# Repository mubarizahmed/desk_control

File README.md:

# desk-control

This is a simple physical widget that sits on your desk and allows you to perform some basic productivity tasks. It works independently of your computer or phone and hence, _in theory_, it should help you focus on your work. It is a work in progress and I will be adding more features as I go along.

<div align="center" style="display: flex; justify-content: center; align-items: center;">

</div>

## Features

- **Current Time** - Displays the current time in a 24-hour format.
- **Weather** - Displays the current temperature, wind, and weather condition (sunny, cloudy, etc.) for a given location.
- **Pomodoro Timer** - A simple timer that helps you focus on your work for a some template amount of time and then take a break. Current implementation is 25 minutes of work and 5 minutes of break. You can change this in the code.
- **Calendar** - Displays the current date and the next 2 events from your Google Calendar. You need to set up a Google script to get the events from your calendar. See the [Google Calendar Setup](#google-calendar-setup) section below.

- **Spotify Control** - Control your Spotify playback (play, pause, next, previous) from the widget.

- **Todoist Integration** - View and complete your upcoming tasks from Todoist.

- **PCB Design** - Single PCB design that can be printed on PCBWay or JLCPCB.

## Planned Features

- **Housing** - 3D printed housing for the PCB and screen.

- **Sensor Integration** - Add more sensors to the project - maybe a temperature sensor, humidity sensor, etc. to get more data from the environment.

- **Widget Details** - Widgets will be clickable and will show more details about the current state. For example, the weather widget will show the hourly forecast for the next 24 hours, the calendar widget will show the events for the next week, etc.

## Hardware Setup (Work in Progress)

The hardware setup is a work in progress. I will be updating this section as I go along. Currently, the hardware setup is:

- **Microcontroller** - ESP32-DevKitC-v4
- **Display** - 2.4" TFT LCD (ILI9341) with SPI interface
- **Rotary Encoder** - KY-040 rotary encoder with push button.

A custom PCB has been designed but not yet tested. The schematic and KiCAD project files are available in the `eda` folder.

<div align="center">
  
</div>

[Schematic](eda/desk_control_schematic_color.png)

<div align="center" style="display: flex; justify-content: center; align-items: center;">

</div>

[PCB Front](eda/front.png) | [PCB Back](eda/back.png)

[KiCAD Project](eda/desk_control)

Pin definitions are given in [here](/main/pin_definitions.h).

## Software Setup

ESP IDF is used to program the ESP32. The project can be configured using `idf.py menuconfig`. The following configuration options are most relevant:

- **ESP_WIFI_SSID** - The SSID of the Wi-Fi network to connect to.
- **ESP_WIFI_PASSWORD** - The password of the Wi-Fi network to connect to.
- **CALENDAR_URL** - The URL of the Google script that returns the events from your calendar.

## Mock UI

The mock UI is a simple representation of what the final UI will look like. It is not a final design and will be updated as I go along. The current design is a simple grid layout with a monotype font which makes absolute positioning of the elements easy.

<div align="center">
  
</div>

## Progress

The project is being prototyped on a breadboard and the hardware setup is a work in progress. The software is being developed in parallel. The current status of the project is shown below:

<div align="center">
  
</div>

## Google Calendar Setup

To get the events from your Google Calendar, you need to set up a Google script that will fetch the events and return them in a JSON format. The script should be deployed as a web app and the URL should be added to the code. The following steps will help you set up the Google script:

1. Go to [Google Apps Script](https://script.google.com/) and create a new project.
2. Copy and paste the code from this (file)[https://github.com/mubarizahmed/desk_control/blob/main/other/calendar.gs] into the script editor
3. Save the project and give it a name.
4. Click on the `Deploy` button and select `New deployment`.
5. Select `Web app` and give it a name.
6. Select `Anyone` under `Who has access` and click on `Deploy`.
7. Authorize the script to access your Google Calendar.
8. Copy the URL of the web app and paste it in the code where it says `CALENDAR_URL`.
9. Save the code and run the script to test it. You should see the events from your calendar in the JSON format.

Thanks to this [blog post](https://www.instructables.com/E-Ink-Family-Calendar-Using-ESP32/) for the idea and the code to get the events from the Google Calendar. The code has been modified to fit the needs of this project.

## Acknowledgements

Thanks to [wttr.in](https://wttr.in/) for the weather API and [Google Calendar API](https://developers.google.com/calendar) for the calendar API.

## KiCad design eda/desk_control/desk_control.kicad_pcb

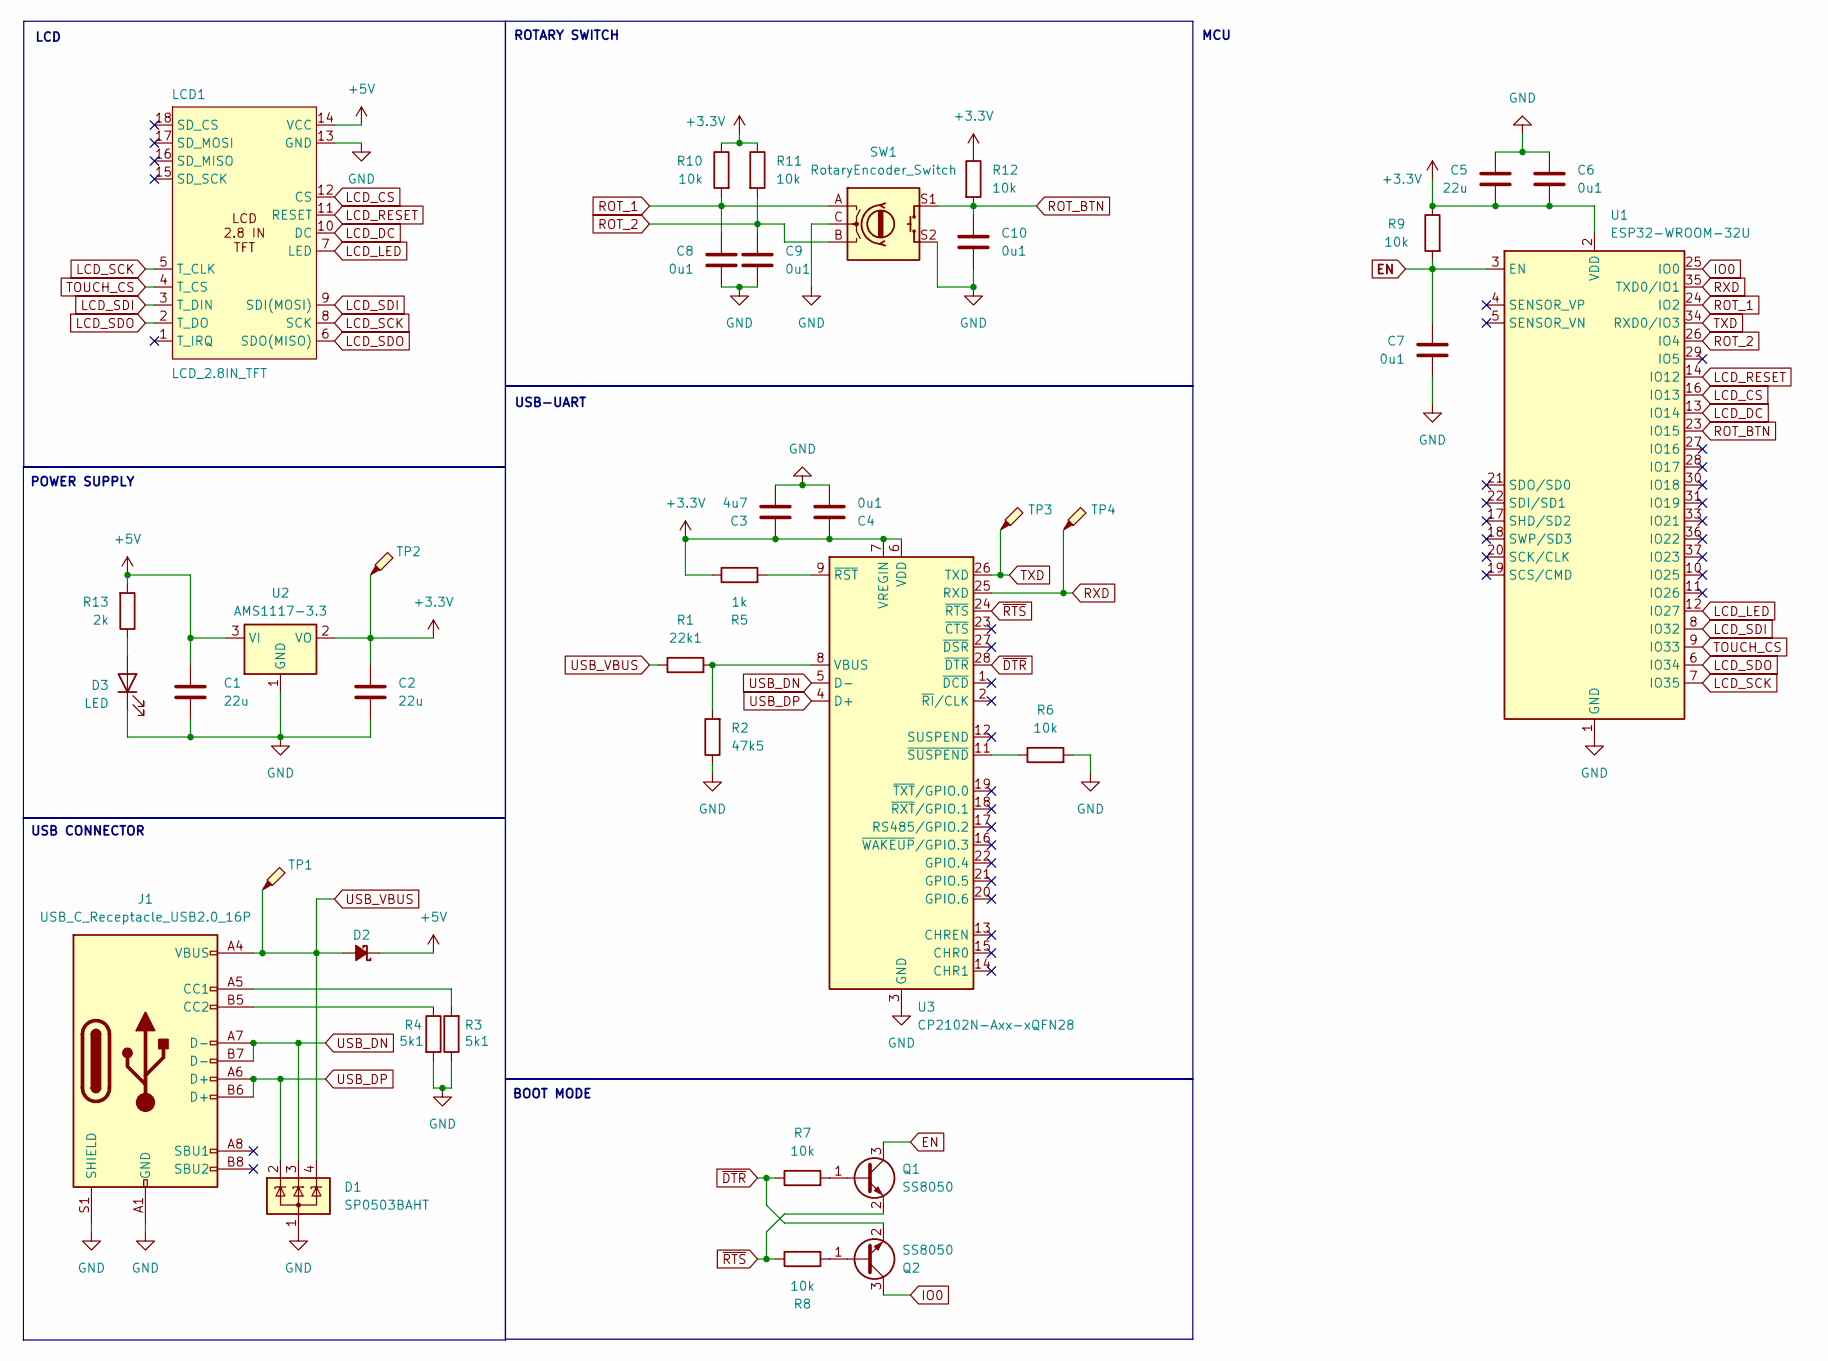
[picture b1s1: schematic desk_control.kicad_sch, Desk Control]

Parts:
C1, C2, C5: 22u; C_1206_3216Metric_Pad1.33x1.80mm_HandSolder
C3: 4u7; C_1206_3216Metric_Pad1.33x1.80mm_HandSolder
C4, C6, C7, C8, C9, C10: 0u1; C_1206_3216Metric_Pad1.33x1.80mm_HandSolder
D1: SP0503BAHT; SOT-143
D2: D_Schottky_Small_Filled; D_SOD-323F
D3: LED; LED_2512_6332Metric
J1: USB_C_Receptacle_USB2.0_16P; USB_C_Receptacle_GCT_USB4110
LCD1: LCD_2.8IN_TFT; LCD_2.8_TFT
Q1, Q2: SS8050; SOT-23
R1: 22k1; R_1206_3216Metric
R2: 47k5; R_1206_3216Metric
R3, R4: 5k1; R_1206_3216Metric
R5: 1k; R_1206_3216Metric
R6, R7, R8, R9, R10, R11, R12: 10k; R_1206_3216Metric
R13: 2k; R_1206_3216Metric
SW1: RotaryEncoder_Switch; Bourns-PEC11R-4220F-S0024-0-0-0
TP1, TP2, TP3, TP4: TestPoint_Probe; TestPoint_Pad_D1.0mm
U1: ESP32-WROOM-32U
U2: AMS1117-3.3; SOT-223-3_TabPin2
U3: CP2102N-Axx-xQFN28; QFN-28-1EP_5x5mm_P0.5mm_EP3.35x3.35mm

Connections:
+3.3V: C2.1, C3.2, C4.1, C5.2, C6.2, R5.1, R9.1, R10.1, R11.1, R12.1, TP2.1, U1.2 (VDD), U2.2 (VO), U3.6 (VDD), U3.7 (VREGIN)
+5V: C1.1, D2.1 (K), LCD1.14 (VCC), R13.2, U2.3 (VI)
EN: C7.1, Q1.3 (C), R9.2, U1.3 (EN)
GND: C1.2, C2.2, C3.1, C4.2, C5.1, C6.1, C7.2, C8.2, C9.2, C10.2, D1.1 (A), D3.1 (K), J1.A1 (GND), J1.A12 (GND), J1.B1 (GND), J1.B12 (GND), J1.S1 (SHIELD), LCD1.13 (GND), R2.1, R3.1, R4.2, R6.2, SW1.C, SW1.S2, U1.1 (GND), U1.15 (GND), U1.38 (GND), U1.39 (GND), U2.1 (GND), U3.3 (GND), U3.29 (GND)
IO0: Q2.3 (C), U1.25 (IO0)
LCD_CS: LCD1.12 (CS), U1.16 (IO13)
LCD_DC: LCD1.10 (DC), U1.13 (IO14)
LCD_LED: LCD1.7 (LED), U1.12 (IO27)
LCD_RESET: LCD1.11 (RESET), U1.14 (IO12)
LCD_SCK: LCD1.5 (T_CLK), LCD1.8 (SCK), U1.7 (IO35)
LCD_SDI: LCD1.3 (T_DIN), LCD1.9 (SDI(MOSI)), U1.8 (IO32)
LCD_SDO: LCD1.2 (T_DO), LCD1.6 (SDO(MISO)), U1.6 (IO34)
unnamed: D3.2 (A), R13.1
unnamed: J1.A5 (CC1), R3.2
unnamed: J1.B5 (CC2), R4.1
unnamed: Q1.1 (B), R7.2
unnamed: Q2.1 (B), R8.2
unnamed: R1.2, R2.2, U3.8 (VBUS)
unnamed: R5.2, U3.9 (~RST)
unnamed: R6.1, U3.11 (~SUSPEND)
ROT_1: C8.1, R10.2, SW1.A, U1.24 (IO2)
ROT_2: C9.1, R11.2, SW1.B, U1.26 (IO4)
ROT_BTN: C10.1, R12.2, SW1.S1, U1.23 (IO15)
RXD: TP4.1, U1.35 (TXD0/IO1), U3.25 (RXD)
TOUCH_CS: LCD1.4 (T_CS), U1.9 (IO33)
TXD: TP3.1, U1.34 (RXD0/IO3), U3.26 (TXD)
USB_DN: D1.3 (K), J1.A7 (D-), J1.B7 (D-), U3.5 (D-)
USB_DP: D1.2 (K), J1.A6 (D+), J1.B6 (D+), U3.4 (D+)
USB_VBUS: D1.4 (K), D2.2 (A), J1.A4 (VBUS), J1.A9 (VBUS), J1.B4 (VBUS), J1.B9 (VBUS), R1.1, TP1.1
~DTR: Q2.2 (E), R7.1, U3.28 (~DTR)
~RTS: Q1.2 (E), R8.1, U3.24 (~RTS)

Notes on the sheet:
LCD
USB-UART
USB CONNECTOR
BOOT MODE
POWER SUPPLY
ROTARY SWITCH
MCU

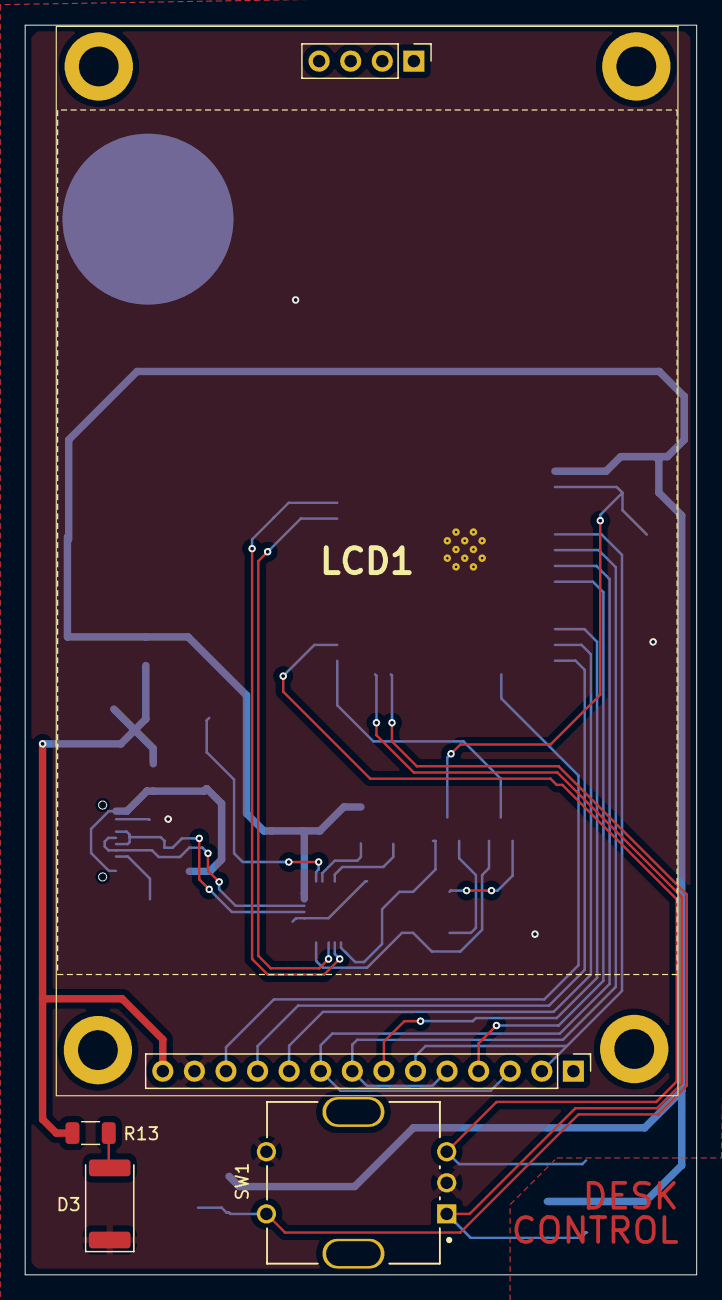
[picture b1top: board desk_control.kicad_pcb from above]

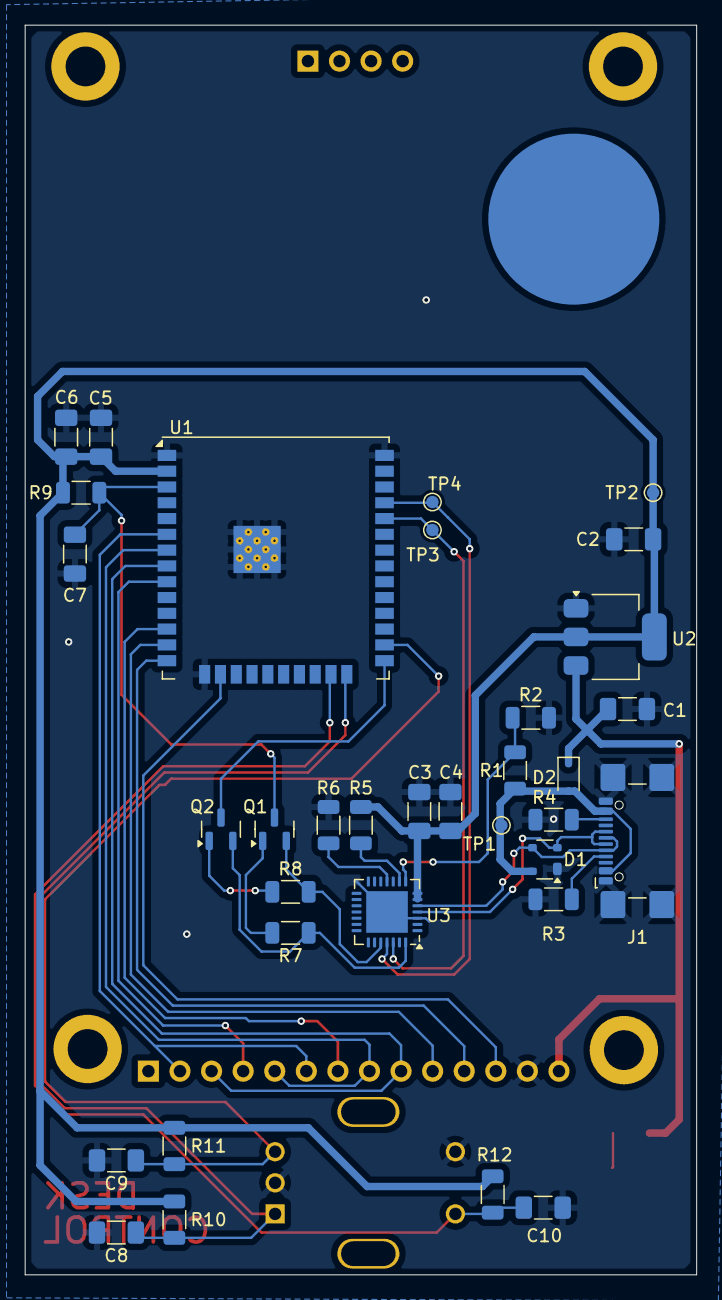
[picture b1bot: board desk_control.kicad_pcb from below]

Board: 2 copper layers, 54.0 x 100.5 mm, 38 parts (34 on the bottom side), 31 nets.

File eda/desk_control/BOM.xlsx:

Reference | Qty | Value | DNP | Exclude from BOM | Exclude from Board | Footprint | Datasheet
C1,C2,C5 | 3 | 22u |  |  |  | Capacitor_SMD:C_1206_3216Metric_Pad1.33x1.80mm_HandSolder | ~
C3 | 1 | 4u7 |  |  |  | Capacitor_SMD:C_1206_3216Metric_Pad1.33x1.80mm_HandSolder | ~
C4,C6,C7,C8,C9,C10 | 6 | 0u1 |  |  |  | Capacitor_SMD:C_1206_3216Metric_Pad1.33x1.80mm_HandSolder | ~
D1 | 1 | SP0503BAHT |  |  |  | Package_TO_SOT_SMD:SOT-143 | http://www.littelfuse.com/~/media/files/littelfuse/technical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
D2 | 1 | D_Schottky_Small_Filled |  |  |  | Diode_SMD:D_SOD-323F | ~
D3 | 1 | LED |  |  |  | LED_SMD:LED_2512_6332Metric | ~
J1 | 1 | USB_C_Receptacle_USB2.0_16P |  |  |  | Connector_USB:USB_C_Receptacle_GCT_USB4110 | https://www.usb.org/sites/default/files/documents/usb_type-c.zip
LCD1 | 1 | LCD_2.8IN_TFT |  |  |  | Custom:LCD_2.8_TFT
Q1,Q2 | 2 | SS8050 |  |  |  | Package_TO_SOT_SMD:SOT-23 | http://www.secosgmbh.com/datasheet/products/SSMPTransistor/S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
R1 | 1 | 22k1 |  |  |  | Resistor_SMD:R_1206_3216Metric | ~
R2 | 1 | 47k5 |  |  |  | Resistor_SMD:R_1206_3216Metric | ~
R3,R4 | 2 | 5k1 |  |  |  | Resistor_SMD:R_1206_3216Metric | ~
R5 | 1 | 1k |  |  |  | Resistor_SMD:R_1206_3216Metric | ~
R6,R7,R8,R9,R10,R11,R12 | 7 | 10k |  |  |  | Resistor_SMD:R_1206_3216Metric | ~
R13 | 1 | 2k |  |  |  | Resistor_SMD:R_1206_3216Metric | ~
SW1 | 1 | RotaryEncoder_Switch |  |  |  | Custom:Bourns-PEC11R-4220F-S0024-0-0-0 | ~
TP1,TP2,TP3,TP4 | 4 | TestPoint_Probe |  |  |  | TestPoint:TestPoint_Pad_D1.0mm | ~
U1 | 1 | ESP32-WROOM-32U |  |  |  | RF_Module:ESP32-WROOM-32U | https://www.espressif.com/sites/default/files/documentation/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
U2 | 1 | AMS1117-3.3 |  |  |  | Package_TO_SOT_SMD:SOT-223-3_TabPin2 | http://www.advanced-monolithic.com/pdf/ds1117.pdf
U3 | 1 | CP2102N-Axx-xQFN28 |  |  |  | Package_DFN_QFN:QFN-28-1EP_5x5mm_P0.5mm_EP3.35x3.35mm | https://www.silabs.com/documents/public/data-sheets/cp2102n-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

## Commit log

2025-04-04 init working lcd, touch
2025-04-05 fix touch calibration
2025-04-06 add WiFi configuration and weather https req
2025-04-09 clean up project
2025-04-09 add weather display
2025-04-10 update rotation, touch calibration, RGB mode
2025-04-10 add time widget
2025-04-10 fix memory leak time task
2025-04-10 add weather widget
2025-04-10 fix mutex for lvgl ui updates
2025-04-11 add date widget
2025-04-11 add calendar widget
2025-04-11 add tasks widget
2025-04-11 add pomodoro widget
2025-04-11 add Spotify widget and refactor UI styles
    - Introduced a new Spotify widget to display current song and artist information.
    - Added buttons for previous, play/pause, and next actions within the Spotify widget.
    - Created a helper function `lv_obj_remove_border_paddin_scrollbar` to streamline the removal of borders and padding from UI objects.
    - Adjusted various UI elements for better alignment and spacing.
    - Updated font references to include additional sizes for better text rendering.
2025-04-11 fix rotated touch
2025-04-11 add pomodoro implementation
2025-04-13 add calendar service
2025-04-16 add description to README.md
2025-04-16 fix README.md
2025-04-18 add spotify auth
2025-04-19 fix mbedtls heap usage
2025-04-19 add spotify get currently playing
2025-04-19 troubleshoot memory, wifi
2025-04-20 add spotify display album cover
2025-04-20 add spotify previous, pause, next on button
2025-04-20 fix play
2025-04-20 fix play memory leak
2025-04-20 fix next track
2025-04-21 add token nvs storage
2025-04-21 fix get_access_token
2025-04-21 add eventgroup signalling for spotify controls
2025-04-21 chore clean up spotify
2025-04-21 chore clean spotify logs, config log level, mbedtls content len, add TODO.md
2025-04-22 add todoist get tasks implementation
2025-04-22 fix random display initialization error
2025-04-22 add event signaling, integrate services
2025-04-22 fix fonts, spotify delay
2025-04-22 chore comments and clean files, add todos
2025-08-13 add schematic, pcb design
